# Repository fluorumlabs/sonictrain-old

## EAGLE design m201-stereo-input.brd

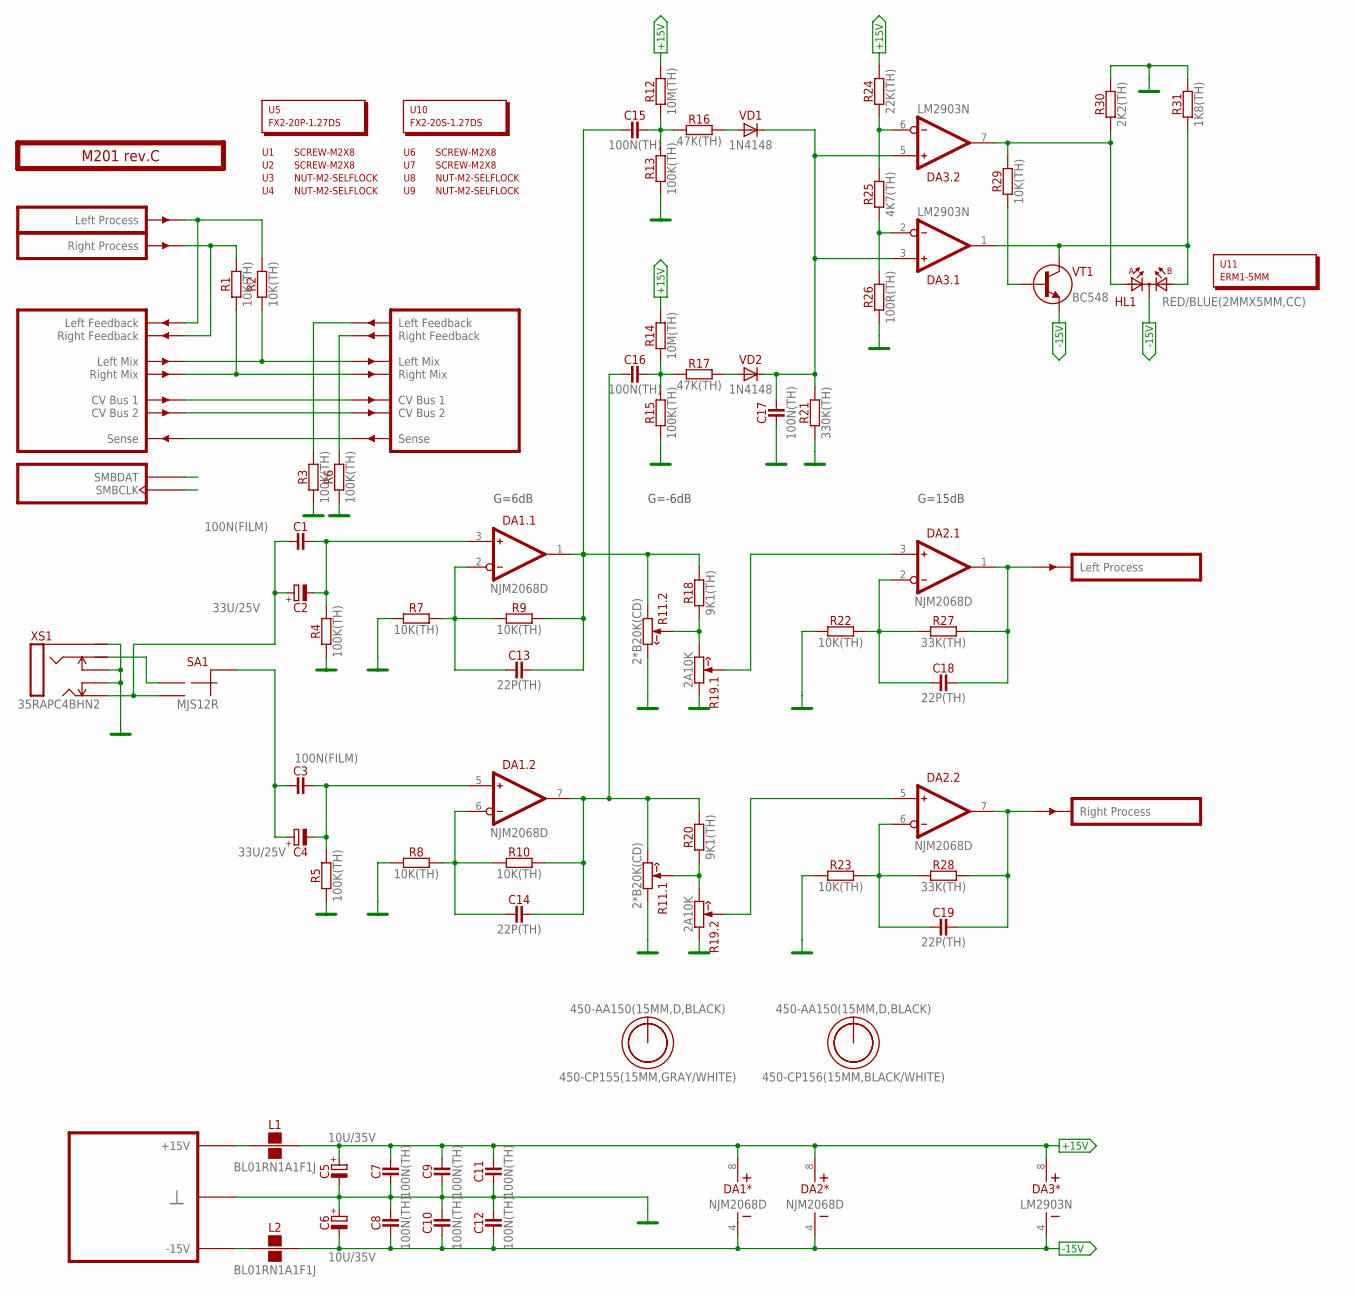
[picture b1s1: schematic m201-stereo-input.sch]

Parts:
C1, C3: 100N(FILM); C050-025X075
C2, C4: 33U/25V; E2,5-7
C5, C6: 10U/35V; E2-5
C7, C8, C9, C10, C11, C12, C15, C16, C17: 100N(TH); C050-024X044
C13, C14, C18, C19: 22P(TH); C050-024X044
DA1, DA2: NJM2068D; DIP-8
DA3: LM2903N; DIP-8
HL1: RED/BLUE(2MMX5MM,CC); LED2X5-3PIN
L1, L2: BL01RN1A1F1J; BL01RN1A
O1, O3: 450-AA150(15MM,D,BLACK); EMPTY
O2: 450-CP155(15MM,GRAY/WHITE); EMPTY
O4: 450-CP156(15MM,BLACK/WHITE); EMPTY
PCB1: M201 rev.C; ST2-BOARD-50
R1, R2, R7, R8, R9, R10, R22, R23, R29: 10K(TH); R-0207/10
R3, R4, R5, R6, R13, R15: 100K(TH); R-0207/10
R11: 2*B20K(CD); RV11-DUAL
R12, R14: 10M(TH); R-0207/10
R16, R17: 47K(TH); R-0207/10
R18, R20: 9K1(TH); R-0207/10
R19: 2A10K; RV11-DUAL
R21: 330K(TH); R-0207/10
R24: 22K(TH); R-0207/10
R25: 4K7(TH); R-0207/10
R26: 100R(TH); R-0207/10
R27, R28: 33K(TH); R-0207/10
R30: 2K2(TH); R-0207/10
R31: 1K8(TH); R-0207/10
SA1: MJS12R; APEM-MJS12R
U1, U2, U6, U7: SCREW-M2X8; EMPTY
U3, U4, U8, U9: NUT-M2-SELFLOCK; EMPTY
U5: FX2-20P-1.27DS; EMPTY
U10: FX2-20S-1.27DS; EMPTY
U11: ERM1-5MM; EMPTY
VD1, VD2: 1N4148; DO35-7
VT1: BC548; TO92
XS1: 35RAPC4BHN2; 35RAP

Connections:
+15V: C5.+, C7.2, C9.2, C11.2, DA1.8 (V+), DA2.8 (V+), DA3.8 (V+), L1.2, R12.2, R14.2, R24.2
-15V: C6.-, C8.1, C10.1, C12.1, DA1.4 (V-), DA2.4 (V-), DA3.4 (V-), HL1.K, L2.2, VT1.3 (E)
GND: C5.-, C6.+, C7.1, C8.2, C9.1, C10.2, C11.1, C12.2, C17.1, PCB1.B4 (GND), PCB1.B4' (GND), PCB1.B5 (GND), PCB1.B5' (GND), PCB1.B6 (GND), PCB1.B6' (GND), PCB1.B7 (GND), PCB1.B7' (GND), PCB1.B8 (GND), PCB1.B8' (GND), R3.1, R4.1, R5.1, R6.1, R7.1, R8.1, R11.1 (CCW), R11.3' (CW), R13.1, R15.1, R19.1 (CCW), R19.1' (CCW), R21.1, R22.1, R23.1, R26.1, R30.2, R31.2, XS1.1 (S), XS1.10 (TN), XS1.11 (RN)
LMIX: PCB1.ALMIX (LMIX), PCB1.ALMIX' (LMIX'), R2.1
unnamed: L1.1, PCB1.A+15 (P+15V), PCB1.A+15' (P+15V), PCB1.B+15 (P+15V), PCB1.B+15' (P+15V)
unnamed: PCB1.ARFBK' (RFBK'), R6.2
unnamed: DA2.3 (IN+), R19.2 (W)
unnamed: PCB1.ALFBK' (LFBK'), R3.2
unnamed: L2.1, PCB1.A-15 (P-15V), PCB1.A-15' (P-15V), PCB1.B-15 (P-15V), PCB1.B-15' (P-15V)
unnamed: SA1.NC (1), XS1.3 (R)
unnamed: C1.1, C2.+, SA1.NO (2), XS1.2 (T)
unnamed: DA2.5 (IN+), R19.2' (W)
unnamed: C3.2, C4.-, DA1.5 (IN+), R5.2
unnamed: C1.2, C2.-, DA1.3 (IN+), R4.2
unnamed: C19.2, DA2.7 (OUT), PCB1.BOUTR' (OUTR), R28.2
unnamed: C18.2, DA2.1 (OUT), PCB1.BOUTL' (OUTL), R27.2
unnamed: C18.1, DA2.2 (IN-), R22.2, R27.1
unnamed: C19.1, DA2.6 (IN-), R23.2, R28.1
unnamed: C14.2, C16.1, DA1.7 (OUT), R10.2, R11.3 (CW), R20.2
unnamed: PCB1.BSENSE (SENSE), PCB1.BSENSE' (SENSE')
unnamed: C15.2, R12.1, R13.2, R16.1
unnamed: C13.2, C15.1, DA1.1 (OUT), R9.2, R11.1' (CCW), R18.2
unnamed: C13.1, DA1.2 (IN-), R7.2, R9.1
unnamed: C14.1, DA1.6 (IN-), R8.2, R10.1
unnamed: R16.2, VD1.A
unnamed: R11.2' (W), R18.1, R19.3 (CW)
unnamed: C16.2, R14.1, R15.2, R17.1
unnamed: R11.2 (W), R19.3' (CW), R20.1
unnamed: C3.1, C4.+, SA1.C (CM)
unnamed: PCB1.ASMBDAT (SMBDAT), PCB1.ASMBDAT' (SMBDAT)
unnamed: PCB1.ARFBK (RFBK), PCB1.BINR (INR), R1.2
unnamed: PCB1.ALFBK (LFBK), PCB1.BINL (INL), R2.2
unnamed: PCB1.ACV1 (CV1), PCB1.ACV1' (CV1')
unnamed: PCB1.ACV2 (CV2), PCB1.ACV2' (CV2')
unnamed: PCB1.ASMBCLK (SMBCLK), PCB1.ASMBCLK' (SMBCLK)
unnamed: R17.2, VD2.A
unnamed: C17.2, DA3.3 (IN+), DA3.5 (IN+), R21.2, VD1.C, VD2.C
unnamed: DA3.2 (IN-), R25.1, R26.2
unnamed: DA3.6 (IN-), R24.1, R25.2
unnamed: DA3.7 (OUT), HL1.A1, R29.2, R30.1
unnamed: R29.1, VT1.2 (B)
unnamed: DA3.1 (OUT), HL1.A2, R31.1, VT1.1 (C)
RMIX: PCB1.ARMIX (RMIX), PCB1.ARMIX' (RMIX'), R1.1

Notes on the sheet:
G=6dB
G=-6dB
G=15dB

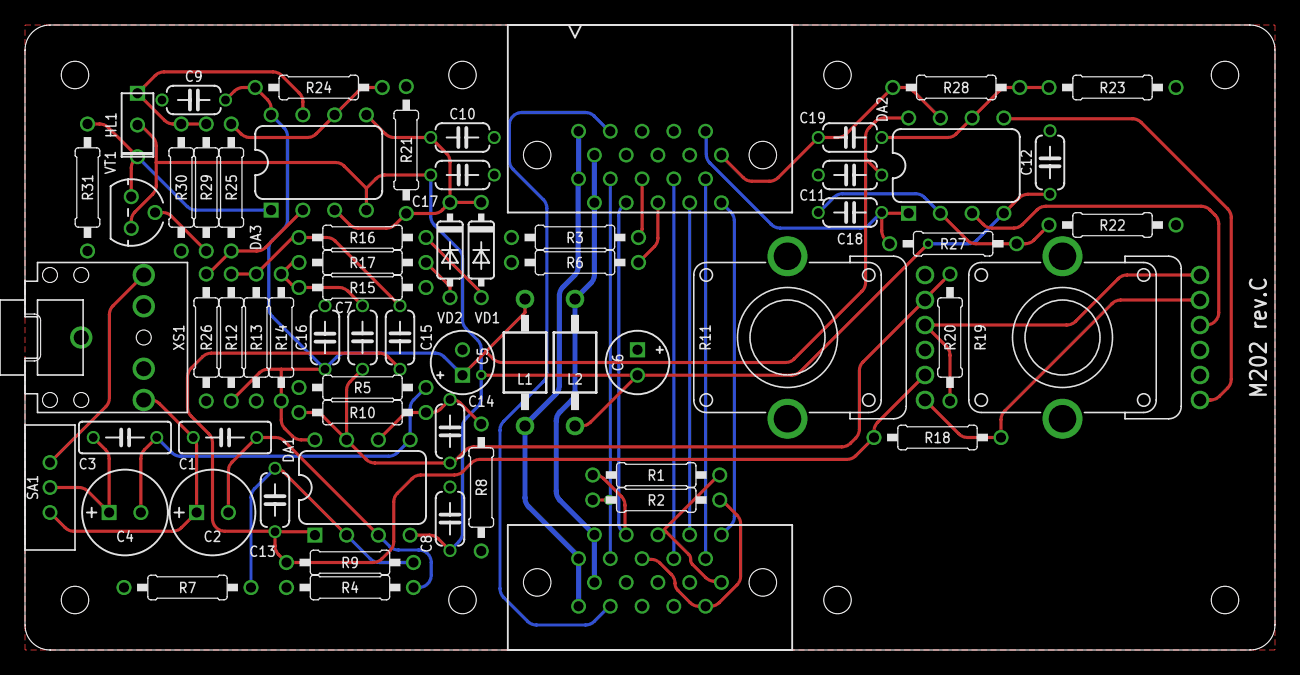
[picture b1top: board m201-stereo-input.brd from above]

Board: 2 copper layers, 100.0 x 50.0 mm, 77 parts (0 on the bottom side), 43 nets.

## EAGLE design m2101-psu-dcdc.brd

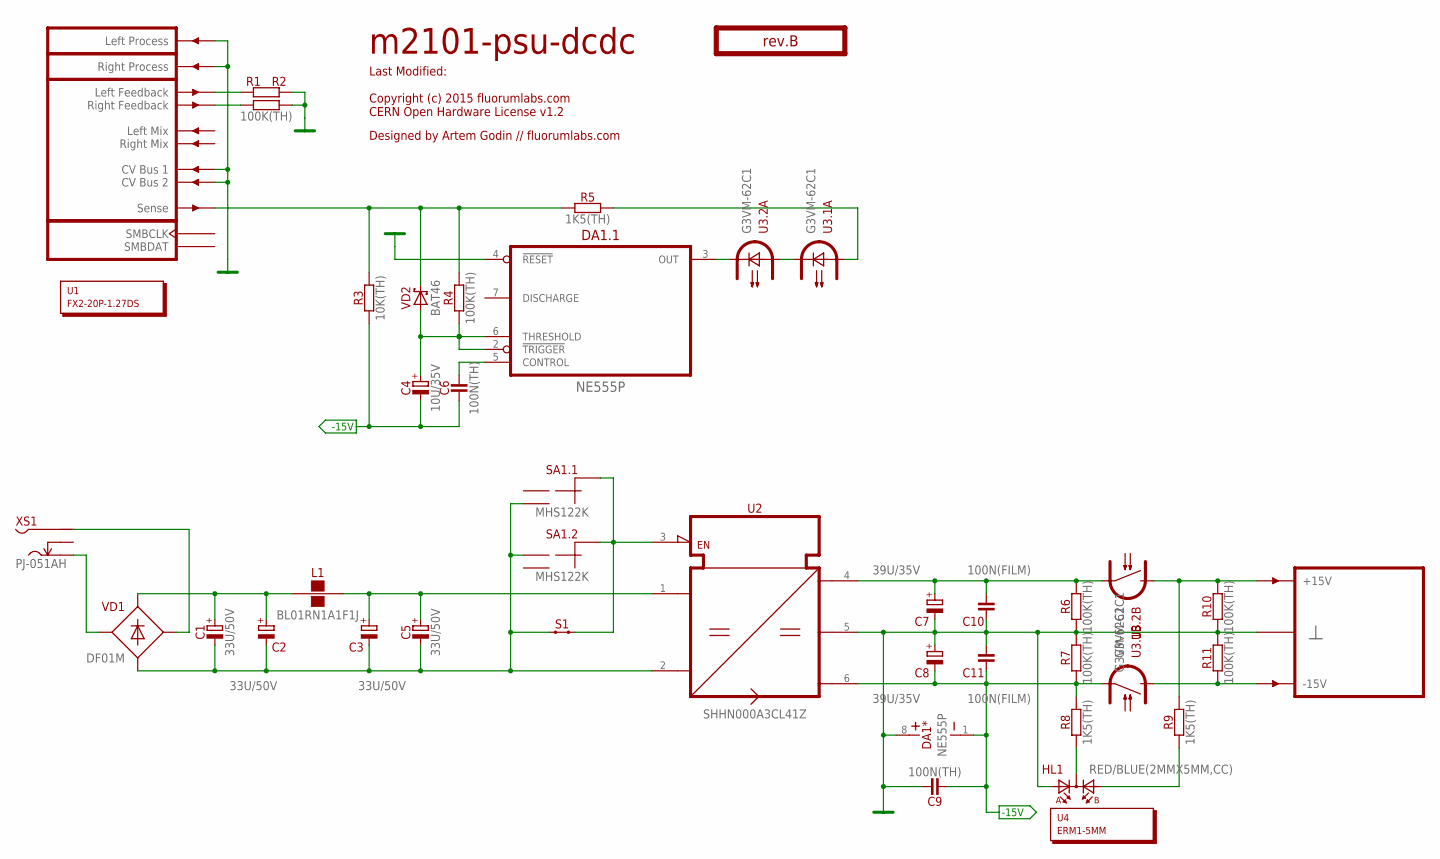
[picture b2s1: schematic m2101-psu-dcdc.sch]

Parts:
C1, C2, C3, C5: 33U/50V; E3,5-8
C4: 10U/35V; E2-5
C6, C9: 100N(TH); C050-024X044
C7, C8: 39U/35V; E3,5-8
C10, C11: 100N(FILM); C050-025X075
DA1: NE555P; DIP-8
HL1: RED/BLUE(2MMX5MM,CC); LED2X5-3PIN
L1: BL01RN1A1F1J; BL01RN1A
O1: Designed by Artem Godin // fluorumlabs.com; EMPTY
PCB1: rev.B; ST2-BOARD-50-PSU
R1, R2, R4, R6, R7, R10, R11: 100K(TH); R-0207/10
R3: 10K(TH); R-0207/10
R5, R8, R9: 1K5(TH); R-0207/10
S1: JUMPER-1POS-SOLDER; JP1-SOLDER
SA1: MHS122K; APEM-MHS122K
U1: FX2-20P-1.27DS; EMPTY
U2: SHHN000A3CL41Z; DC/DC-C1
U3: G3VM-62C1; DIL08
U4: ERM1-5MM; EMPTY
VD1: DF01M; MDIP-4
VD2: BAT46; DO35-7
XS1: PJ-051AH

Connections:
-15V: C4.-, C6.1, C8.-, C9.1, C11.1, DA1.1 (V-), R3.1, R7.1, R8.2, U2.6 (V-), U3.7 (S2)
GND: C7.-, C8.+, C9.2, C10.1, C11.2, DA1.4 (!RESET), DA1.8 (V+), HL1.A1, PCB1.ACV1' (CV1'), PCB1.ACV2' (CV2'), PCB1.B4' (GND), PCB1.B5' (GND), PCB1.B6' (GND), PCB1.B7' (GND), PCB1.B8' (GND), PCB1.BOUTL' (OUTL), PCB1.BOUTR' (OUTR), R1.2, R2.2, R6.1, R7.2, R10.1, R11.2, U2.5 (GND)
unnamed: R5.2, U3.1 (A)
unnamed: VD1.1 (AC1), XS1.3 (S)
unnamed: C1.-, C2.-, C3.-, C5.-, S1.1, SA1.1' (1), SA1.2, U2.2 (IN-), VD1.4 (A)
unnamed: PCB1.ALFBK' (LFBK'), R1.1
unnamed: PCB1.ARFBK' (RFBK'), R2.1
unnamed: C6.2, DA1.5 (CONTROL)
unnamed: DA1.3 (OUT), U3.4 (C)
unnamed: PCB1.A+15' (P+15V), PCB1.B+15' (P+15V), R9.2, R10.2, U3.6 (S1)
unnamed: U3.2 (C), U3.3 (A)
unnamed: C4.+, DA1.2 (!TRIGGER), DA1.6 (THRESHOLD), R4.1, VD2.A
unnamed: VD1.2 (AC2), XS1.1
unnamed: PCB1.A-15' (P-15V), PCB1.B-15' (P-15V), R11.1, U3.8 (S1)
unnamed: HL1.K, R8.1
unnamed: HL1.A2, R9.1
unnamed: C7.+, C10.2, R6.2, U2.4 (V+), U3.5 (S2)
unnamed: S1.2, SA1.CMN (CM), SA1.CMN' (CM), U2.3 (EN)
unnamed: C1.+, C2.+, L1.1, VD1.3 (C)
unnamed: C3.+, C5.+, L1.2, U2.1 (IN+)
SENSE: PCB1.BSENSE' (SENSE'), R3.2, R4.2, R5.1, VD2.C

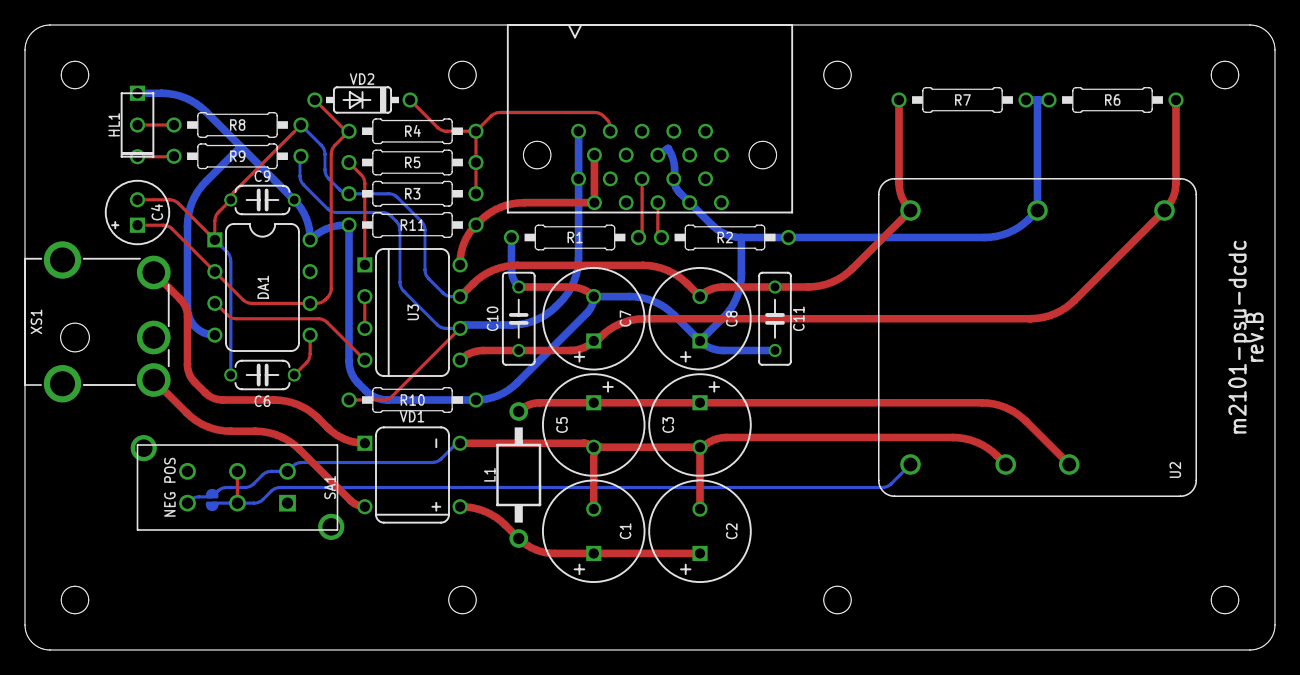
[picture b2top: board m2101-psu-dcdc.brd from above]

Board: 2 copper layers, 100.0 x 50.0 mm, 36 parts (1 on the bottom side), 21 nets.

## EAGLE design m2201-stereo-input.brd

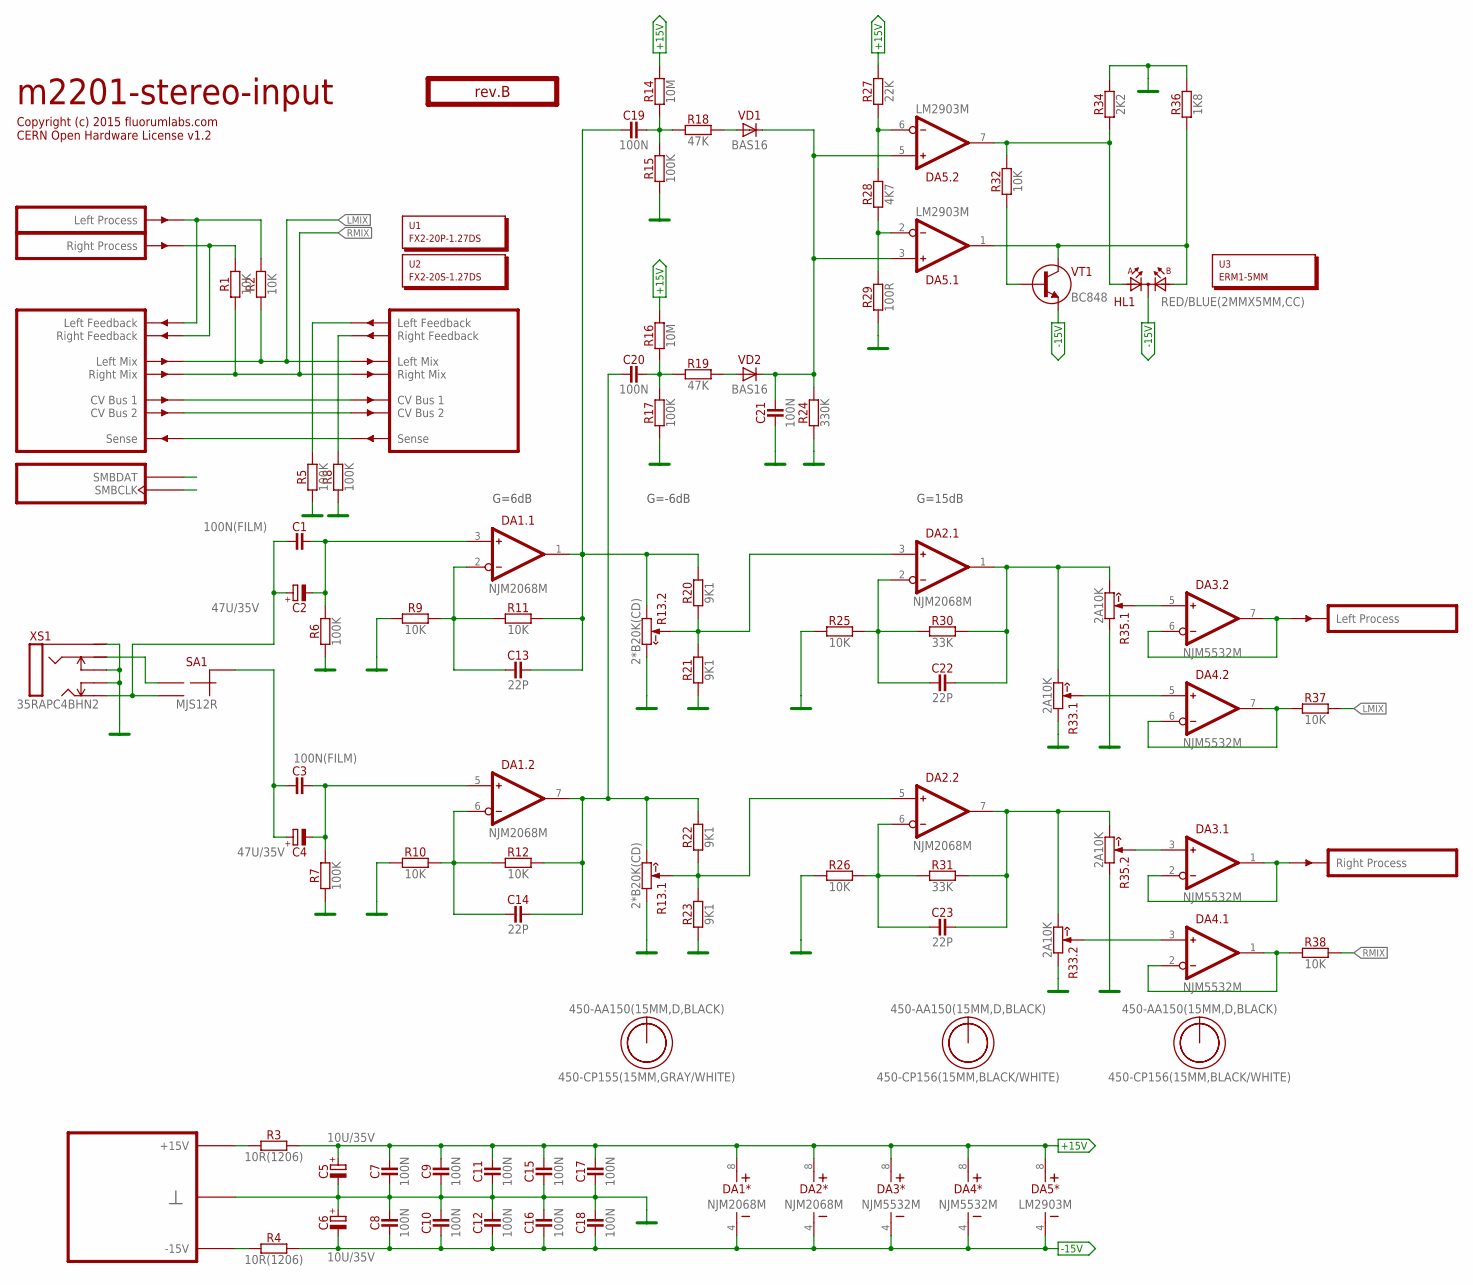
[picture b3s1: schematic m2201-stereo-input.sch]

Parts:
C1, C3: 100N(FILM); C050-025X075
C2, C4: 47U/35V; E3,5-8
C5, C6: 10U/35V; E2-5
C7, C8, C9, C10, C11, C12, C15, C16, C17, C18, C19, C20, C21: 100N; C-0805
C13, C14, C22, C23: 22P; C-0805
DA1, DA2: NJM2068M; SO-8
DA3, DA4: NJM5532M; SO-8
DA5: LM2903M; SO-8
HL1: RED/BLUE(2MMX5MM,CC); LED2X5-3PIN
O1: TITLE; EMPTY
O2, O4, O6: 450-AA150(15MM,D,BLACK); EMPTY
O3: 450-CP155(15MM,GRAY/WHITE); EMPTY
O5, O7: 450-CP156(15MM,BLACK/WHITE); EMPTY
PCB1: rev.B; ST2-BOARD-50
R1, R2, R9, R10, R11, R12, R25, R26, R32, R37, R38: 10K; R-0805
R3, R4: 10R(1206); R-1206
R5, R6, R7, R8, R15, R17: 100K; R-0805
R13: 2*B20K(CD); RV11-DUAL
R14, R16: 10M; R-0805
R18, R19: 47K; R-0805
R20, R21, R22, R23: 9K1; R-0805
R24: 330K; R-0805
R27: 22K; R-0805
R28: 4K7; R-0805
R29: 100R; R-0805
R30, R31: 33K; R-0805
R33, R35: 2A10K; RV11-DUAL
R34: 2K2; R-0805
R36: 1K8; R-0805
SA1: MJS12R; APEM-MJS12R
U1: FX2-20P-1.27DS; EMPTY
U2: FX2-20S-1.27DS; EMPTY
U3: ERM1-5MM; EMPTY
VD1, VD2: BAS16; SOT23
VT1: BC848; SOT23
XS1: 35RAPC4BHN2; 35RAP

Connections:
+15V: C5.+, C7.2, C9.2, C11.2, C15.2, C17.2, DA1.8 (V+), DA2.8 (V+), DA3.8 (V+), DA4.8 (V+), DA5.8 (V+), R3.2, R14.2, R16.2, R27.2
-15V: C6.-, C8.1, C10.1, C12.1, C16.1, C18.1, DA1.4 (V-), DA2.4 (V-), DA3.4 (V-), DA4.4 (V-), DA5.4 (V-), HL1.K, R4.2, VT1.2 (E)
GND: C5.-, C6.+, C7.1, C8.2, C9.1, C10.2, C11.1, C12.2, C15.1, C16.2, C17.1, C18.2, C21.1, PCB1.B4 (GND), PCB1.B4' (GND), PCB1.B5 (GND), PCB1.B5' (GND), PCB1.B6 (GND), PCB1.B6' (GND), PCB1.B7 (GND), PCB1.B7' (GND), PCB1.B8 (GND), PCB1.B8' (GND), R5.1, R6.1, R7.1, R8.1, R9.1, R10.1, R13.1 (CCW), R13.3' (CW), R15.1, R17.1, R21.1, R23.1, R24.1, R25.1, R26.1, R29.1, R33.1 (CCW), R33.1' (CCW), R34.2, R35.1 (CCW), R35.1' (CCW), R36.2, XS1.1 (S), XS1.10 (TN), XS1.11 (RN)
LMIX: PCB1.ALMIX (LMIX), PCB1.ALMIX' (LMIX'), R2.1, R37.2
unnamed: PCB1.A+15 (P+15V), PCB1.A+15' (P+15V), PCB1.B+15 (P+15V), PCB1.B+15' (P+15V), R3.1
unnamed: PCB1.ARFBK' (RFBK'), R8.2
unnamed: DA2.3 (IN+), R13.2' (W), R20.1, R21.2
unnamed: PCB1.ALFBK' (LFBK'), R5.2
unnamed: PCB1.A-15 (P-15V), PCB1.A-15' (P-15V), PCB1.B-15 (P-15V), PCB1.B-15' (P-15V), R4.1
unnamed: SA1.NC (1), XS1.3 (R)
unnamed: C1.1, C2.+, SA1.NO (2), XS1.2 (T)
unnamed: DA2.5 (IN+), R13.2 (W), R22.1, R23.2
unnamed: C3.2, C4.-, DA1.5 (IN+), R7.2
unnamed: C1.2, C2.-, DA1.3 (IN+), R6.2
unnamed: C23.2, DA2.7 (OUT), R31.2, R33.3' (CW), R35.3' (CW)
unnamed: C22.2, DA2.1 (OUT), R30.2, R33.3 (CW), R35.3 (CW)
unnamed: C22.1, DA2.2 (IN-), R25.2, R30.1
unnamed: C23.1, DA2.6 (IN-), R26.2, R31.1
unnamed: C14.2, C20.1, DA1.7 (OUT), R12.2, R13.3 (CW), R22.2
unnamed: PCB1.BSENSE (SENSE), PCB1.BSENSE' (SENSE')
unnamed: C19.2, R14.1, R15.2, R18.1
unnamed: DA3.6 (IN-), DA3.7 (OUT), PCB1.BOUTL' (OUTL)
unnamed: C13.2, C19.1, DA1.1 (OUT), R11.2, R13.1' (CCW), R20.2
unnamed: DA4.6 (IN-), DA4.7 (OUT), R37.1
unnamed: DA3.1 (OUT), DA3.2 (IN-), PCB1.BOUTR' (OUTR)
unnamed: DA4.1 (OUT), DA4.2 (IN-), R38.1
unnamed: DA3.5 (IN+), R35.2 (W)
unnamed: DA4.5 (IN+), R33.2 (W)
unnamed: DA3.3 (IN+), R35.2' (W)
unnamed: C13.1, DA1.2 (IN-), R9.2, R11.1
unnamed: C14.1, DA1.6 (IN-), R10.2, R12.1
unnamed: DA4.3 (IN+), R33.2' (W)
unnamed: R18.2, VD1.1 (A)
unnamed: C20.2, R16.1, R17.2, R19.1
unnamed: C3.1, C4.+, SA1.C (CM)
unnamed: PCB1.ASMBDAT (SMBDAT), PCB1.ASMBDAT' (SMBDAT)
unnamed: PCB1.ARFBK (RFBK), PCB1.BINR (INR), R1.2
unnamed: PCB1.ALFBK (LFBK), PCB1.BINL (INL), R2.2
unnamed: PCB1.ACV1 (CV1), PCB1.ACV1' (CV1')
unnamed: PCB1.ACV2 (CV2), PCB1.ACV2' (CV2')
unnamed: PCB1.ASMBCLK (SMBCLK), PCB1.ASMBCLK' (SMBCLK)
unnamed: R19.2, VD2.1 (A)
unnamed: C21.2, DA5.3 (IN+), DA5.5 (IN+), R24.2, VD1.2 (C), VD2.2 (C)
unnamed: DA5.2 (IN-), R28.1, R29.2
unnamed: DA5.6 (IN-), R27.1, R28.2
unnamed: DA5.7 (OUT), HL1.A1, R32.2, R34.1
unnamed: R32.1, VT1.1 (B)
unnamed: DA5.1 (OUT), HL1.A2, R36.1, VT1.3 (C)
RMIX: PCB1.ARMIX (RMIX), PCB1.ARMIX' (RMIX'), R1.1, R38.2

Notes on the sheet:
G=6dB
G=-6dB
G=15dB

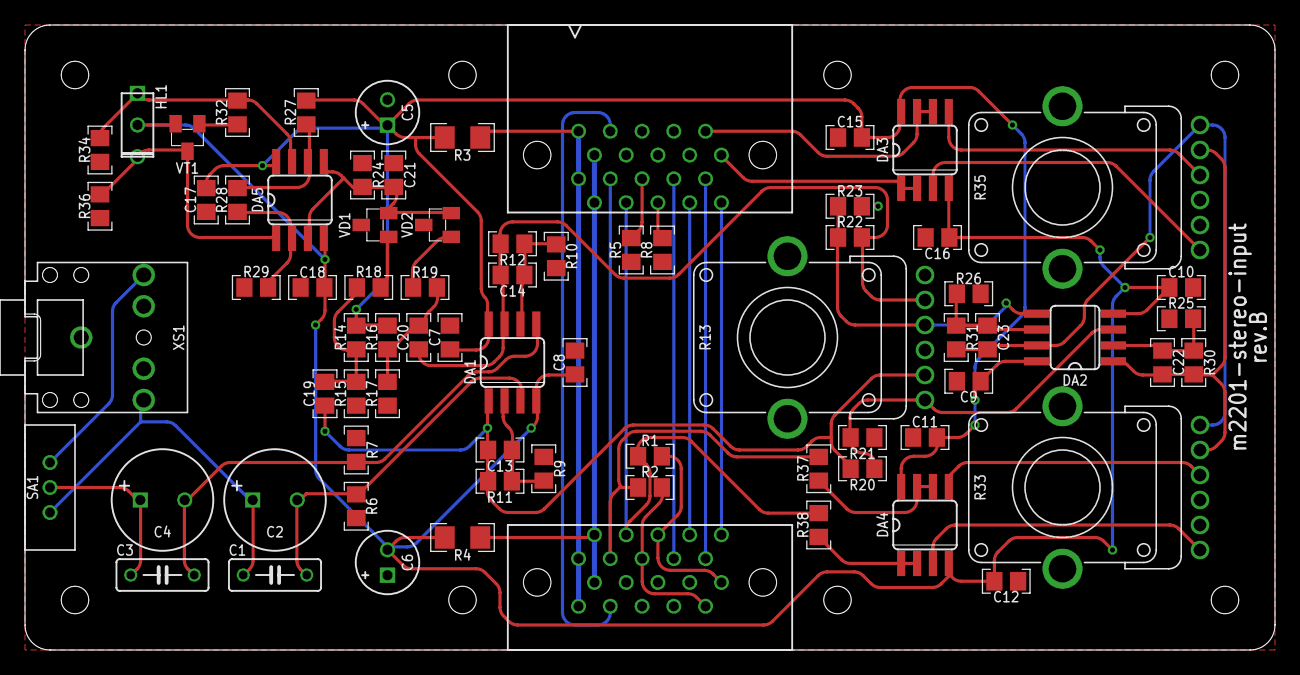
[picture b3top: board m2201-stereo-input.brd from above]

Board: 2 copper layers, 100.0 x 50.0 mm, 83 parts (0 on the bottom side), 49 nets.

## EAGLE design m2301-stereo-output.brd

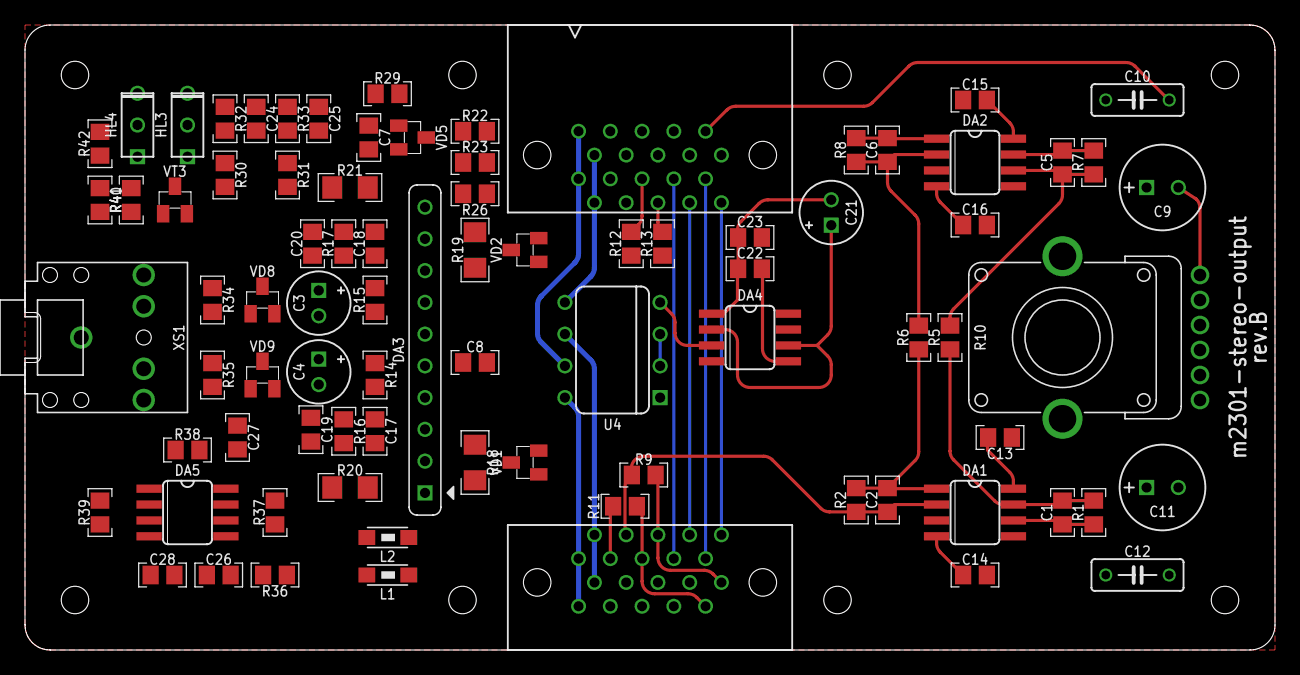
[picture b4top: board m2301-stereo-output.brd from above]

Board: 2 copper layers, 100.0 x 50.0 mm, 89 parts (0 on the bottom side), 52 nets.

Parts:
C1, C2, C5, C6, C17, C18: 22P; C-0805
C3, C4, C21: 10U/35V; E2-5
C7, C8, C13, C14, C15, C16, C19, C20, C22, C23, C24, C25, C26, C27, C28: 100N; C-0805
C9, C11: 33U/25V; E2,5-7
C10, C12: 100N(FILM); C050-025X075
DA1, DA2: NJM2068M; SO-8
DA3: LA6515; SIL10
DA4: NE555D; SO-8
DA5: LM2903M; SO-8
HL3, HL4: RED/BLUE(2MMX5MM,CC); LED2X5-3PIN
L1, L2: BLM31AJ601SN1L; 1206
O1: EMPTY
O2: 450-AA150(15MM,D,BLACK); EMPTY
O3: 450-CP156(15MM,BLACK/WHITE); EMPTY
PCB1: rev.B; ST2-BOARD-50
R1, R2, R5, R6, R7, R8, R9, R11, R14, R15, R22, R41: 10K; R-0805
R10: 2*A10K; RV11-DUAL
R12, R13, R23, R32, R33: 100K; R-0805
R16, R17: 33K; R-0805
R18, R19: 10R(1206); R-1206
R20, R21: 2R(1206); R-1206
R26: 1K5; R-0805
R29: 3K3; R-0805
R30, R31: 10M; R-0805
R34, R35: 47K; R-0805
R36: 330K; R-0805
R37: 22K; R-0805
R38: 4K7; R-0805
R39: 100R; R-0805
R40: 2K2; R-0805
R42: 1K8; R-0805
U1, U7: ERM1-5MM; EMPTY
U4: G3VM-62C1; DIL08
U5: FX2-20P-1.27DS; EMPTY
U6: FX2-20S-1.27DS; EMPTY
VD1, VD2: BAV199; SOT23
VD5, VD8, VD9: BAS16; SOT23
VT3: BC848; SOT23
XS1: 35RAPC4BHN2; 35RAP

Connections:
+15V: C3.+, C7.2, C13.2, C15.2, C27.2, DA1.8, DA2.8, DA3.10, DA5.8, L1.2, R30.2, R31.2, R37.2, VD1.2, VD2.2
-15V: C4.-, C8.1, C14.1, C16.1, C21.-, C22.1, C23.1, C28.1, DA1.4, DA2.4, DA3.5, DA4.1, DA5.4, HL3.K, HL4.K, L2.2, R22.1, VD1.1, VD2.1, VT3.2
CHAIN+15: PCB1.A+15', PCB1.B+15', R29.2, U4.7
GND: C3.-, C4.+, C7.1, C8.2, C13.1, C14.2, C15.1, C16.2, C19.1, C20.1, C23.2, C26.1, C27.1, C28.2, DA1.3, DA1.5, DA2.3, DA2.5, DA4.4, DA4.8, PCB1.B4, PCB1.B4', PCB1.B5, PCB1.B5', PCB1.B6, PCB1.B6', PCB1.B7, PCB1.B7', PCB1.B8, PCB1.B8', PCB1.BSENSE, R10.1, R10.1', R12.1, R13.1, R14.1, R15.1, R32.1, R33.1, R36.1, R39.1, R40.2, R42.2, XS1.1
LMIX: C1.1, DA1.6, PCB1.ALMIX, R1.1, R11.1
unnamed: L1.1, PCB1.A+15, PCB1.B+15, U4.8
unnamed: PCB1.ARFBK', R13.2
unnamed: DA3.6, R10.2
unnamed: PCB1.ALFBK', R12.2
unnamed: L2.1, PCB1.A-15, PCB1.B-15, U4.6
unnamed: C1.2, DA1.7, R1.2, R5.1
unnamed: C2.2, DA1.1, R2.2, R6.1
unnamed: DA3.4, R10.2'
unnamed: C11.-, C12.2, C25.1, PCB1.BOUTR', R10.3
unnamed: C17.2, DA3.1, R16.2, R18.2, R20.2, VD1.3, XS1.2
unnamed: C17.1, DA3.3, R14.2, R16.1
unnamed: R34.2, VD8.1
unnamed: DA3.2, R18.1
unnamed: C9.-, C10.2, C24.1, PCB1.BOUTL', R10.3'
unnamed: C19.2, R20.1
unnamed: C24.2, R30.1, R32.2, R34.1
unnamed: C25.2, R31.1, R33.2, R35.1
unnamed: R35.2, VD9.1
unnamed: C26.2, DA5.3, DA5.5, R36.2, VD8.2, VD9.2
unnamed: C18.1, DA3.7, R15.2, R17.1
unnamed: DA5.2, R38.1, R39.2
unnamed: C18.2, DA3.9, R17.2, R19.2, R21.2, VD2.3, XS1.3
unnamed: DA5.1, HL4.A2, R42.1, VT3.3
unnamed: C22.2, DA4.5
unnamed: C21.+, DA4.2, DA4.6, R23.1, VD5.1
unnamed: R26.2, U4.1
unnamed: DA4.3, U4.4
unnamed: U4.2, U4.3
unnamed: PCB1.ASMBDAT, PCB1.ASMBDAT'
unnamed: PCB1.ARFBK, PCB1.BINR, R9.2
unnamed: PCB1.ALFBK, PCB1.BINL, R11.2
unnamed: PCB1.ACV1, PCB1.ACV1'
unnamed: PCB1.ACV2, PCB1.ACV2'
unnamed: PCB1.ASMBCLK, PCB1.ASMBCLK'
unnamed: HL3.A2, R29.1
unnamed: DA3.8, R19.1
unnamed: C20.2, R21.1
unnamed: DA5.6, R37.1, R38.2
unnamed: DA5.7, HL4.A1, R40.1, R41.2
unnamed: R41.1, VT3.1
unnamed: PCB1.A-15', PCB1.B-15', U4.5
unnamed: C5.1, DA2.6, R5.2, R7.1
unnamed: C5.2, C9.+, C10.1, DA2.7, R7.2
unnamed: C6.1, DA2.2, R6.2, R8.1
unnamed: C6.2, C11.+, C12.1, DA2.1, R8.2
RMIX: C2.1, DA1.2, PCB1.ARMIX, R2.1, R9.1
SENSE: PCB1.BSENSE', R22.2, R23.2, R26.1, VD5.2

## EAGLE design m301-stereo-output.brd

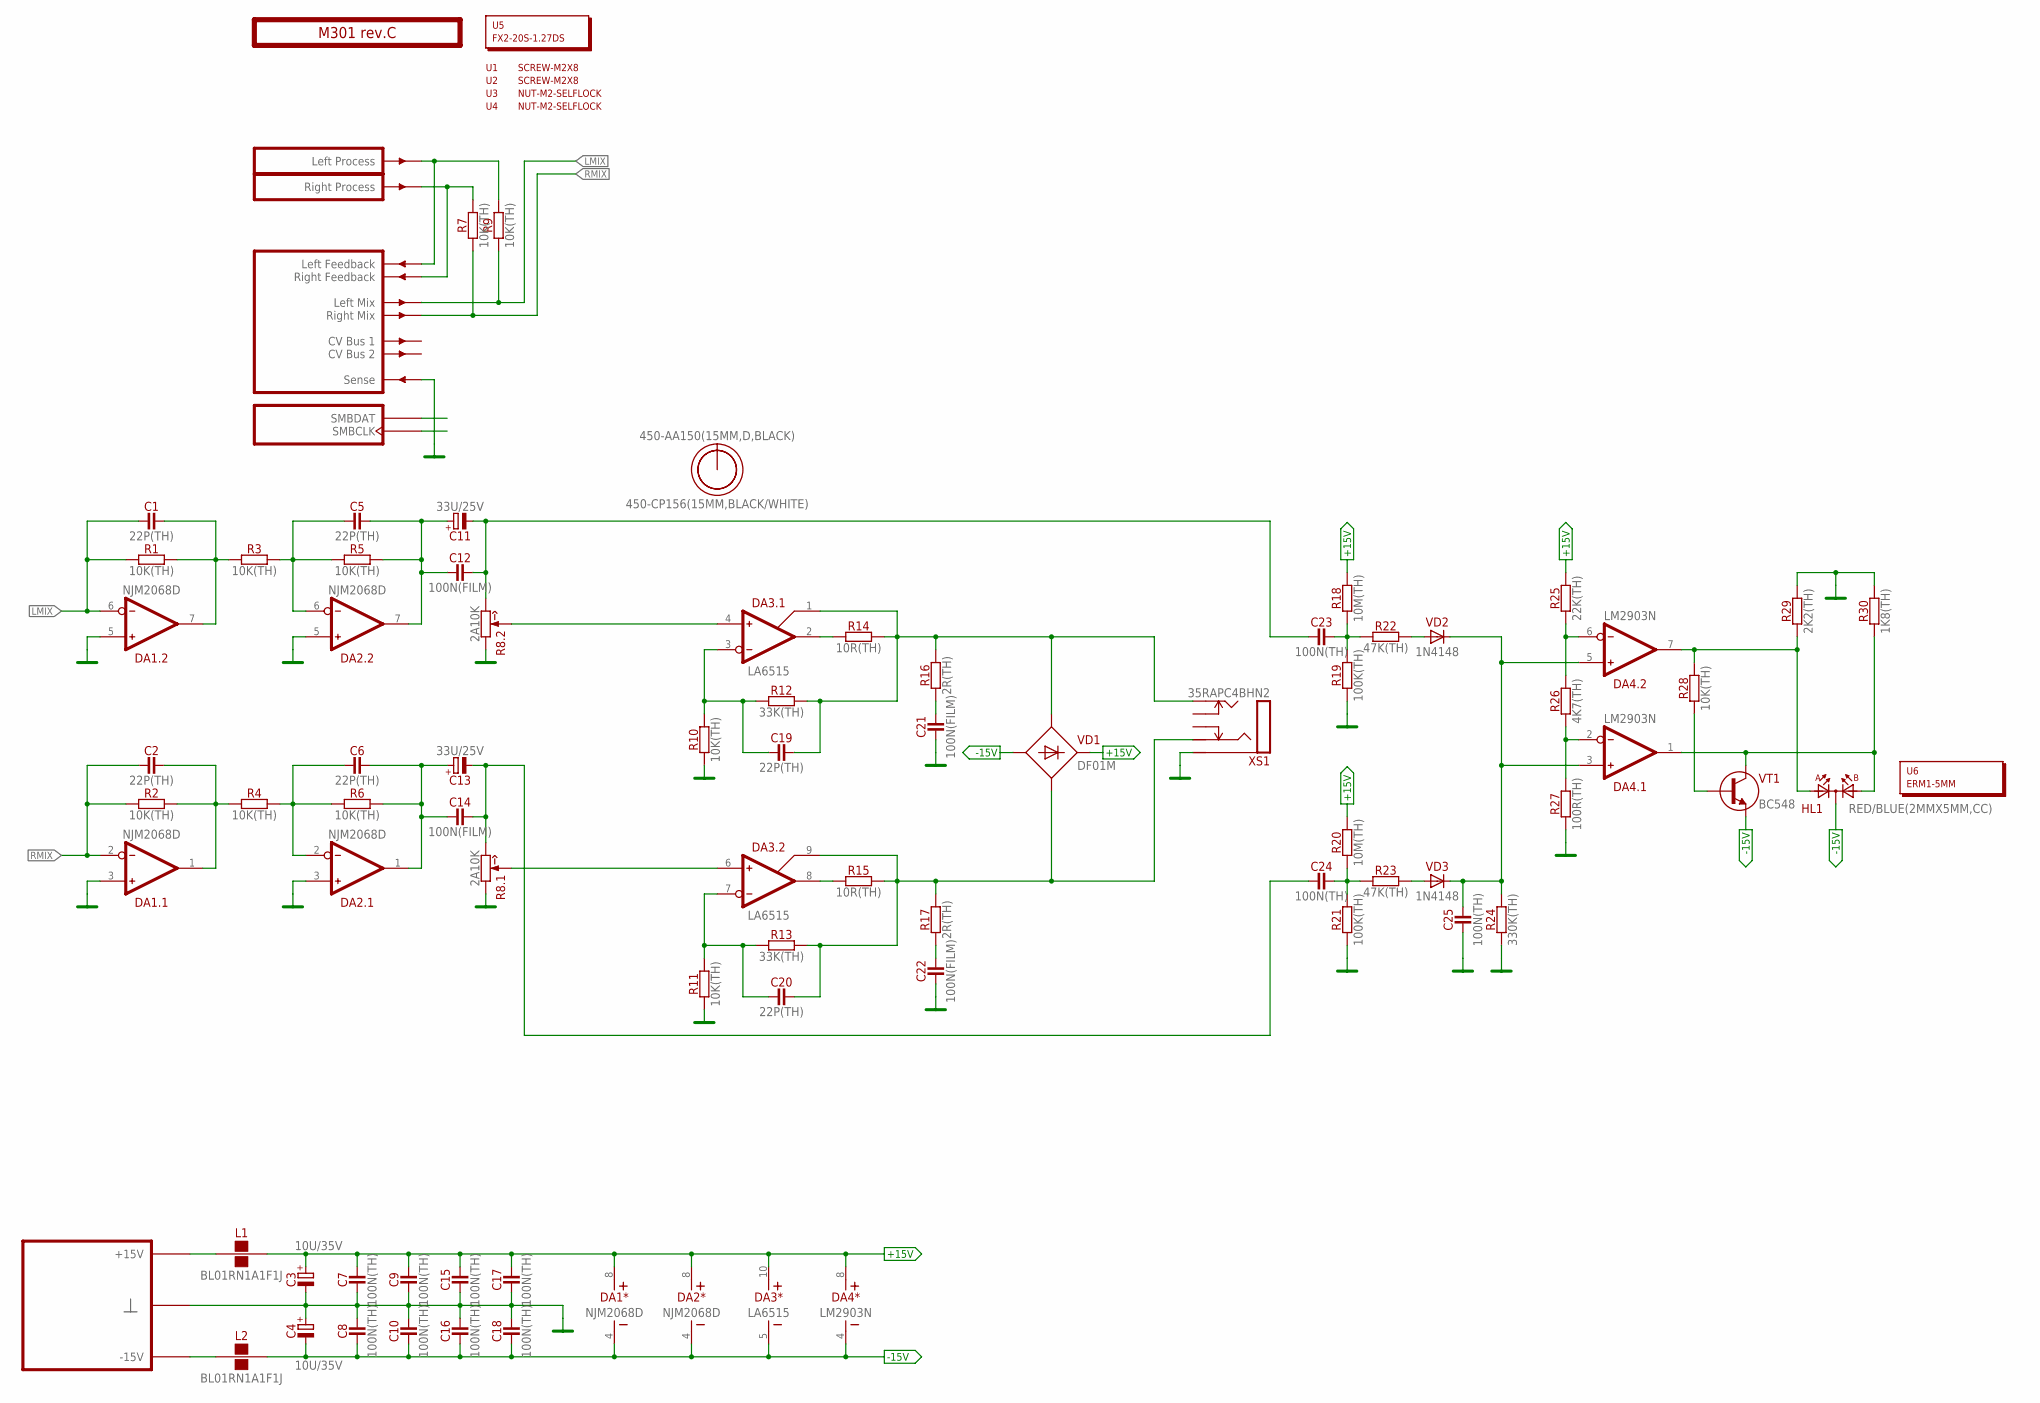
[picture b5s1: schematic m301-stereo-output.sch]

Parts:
C1, C2, C5, C6, C19, C20: 22P(TH); C050-024X044
C3, C4: 10U/35V; E2-5
C7, C8, C9, C10, C15, C16, C17, C18, C23, C24, C25: 100N(TH); C050-024X044
C11, C13: 33U/25V; E2,5-7
C12, C14, C21, C22: 100N(FILM); C050-025X075
DA1, DA2: NJM2068D; DIP-8
DA3: LA6515; SIL10
DA4: LM2903N; DIP-8
HL1: RED/BLUE(2MMX5MM,CC); LED2X5-3PIN
L1, L2: BL01RN1A1F1J; BL01RN1A
O1: 450-AA150(15MM,D,BLACK); EMPTY
O2: 450-CP156(15MM,BLACK/WHITE); EMPTY
PCB1: M301 rev.C; ST2-BOARD-50-END
R1, R2, R3, R4, R5, R6, R7, R9, R10, R11, R28: 10K(TH); R-0207/10
R8: 2A10K; RV11-DUAL
R12, R13: 33K(TH); R-0207/10
R14, R15: 10R(TH); R-0207/10
R16, R17: 2R(TH); R-0207/10
R18, R20: 10M(TH); R-0207/10
R19, R21: 100K(TH); R-0207/10
R22, R23: 47K(TH); R-0207/10
R24: 330K(TH); R-0207/10
R25: 22K(TH); R-0207/10
R26: 4K7(TH); R-0207/10
R27: 100R(TH); R-0207/10
R29: 2K2(TH); R-0207/10
R30: 1K8(TH); R-0207/10
U1, U2: SCREW-M2X8; EMPTY
U3, U4: NUT-M2-SELFLOCK; EMPTY
U5: FX2-20S-1.27DS; EMPTY
U6: ERM1-5MM; EMPTY
VD1: DF01M; MDIP-4
VD2, VD3: 1N4148; DO35-7
VT1: BC548; TO92
XS1: 35RAPC4BHN2; 35RAP

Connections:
+15V: C3.+, C7.2, C9.2, C15.2, C17.2, DA1.8 (V+), DA2.8 (V+), DA3.10 (V+), DA4.8 (V+), L1.2, R18.2, R20.2, R25.2, VD1.3 (C)
-15V: C4.-, C8.1, C10.1, C16.1, C18.1, DA1.4 (V-), DA2.4 (V-), DA3.5 (V-), DA4.4 (V-), HL1.K, L2.2, VD1.4 (A), VT1.3 (E)
GND: C3.-, C4.+, C7.1, C8.2, C9.1, C10.2, C15.1, C16.2, C17.1, C18.2, C21.1, C22.1, C25.1, DA1.3 (IN+), DA1.5 (IN+), DA2.3 (IN+), DA2.5 (IN+), PCB1.B4 (GND), PCB1.B5 (GND), PCB1.B6 (GND), PCB1.B7 (GND), PCB1.B8 (GND), PCB1.BSENSE (SENSE), R8.1 (CCW), R8.1' (CCW), R10.1, R11.1, R19.1, R21.1, R24.1, R27.1, R29.2, R30.2, XS1.1 (S)
LMIX: C1.1, DA1.6 (IN-), PCB1.ALMIX (LMIX), R1.1, R9.1
unnamed: L1.1, PCB1.A+15 (P+15V), PCB1.B+15 (P+15V)
unnamed: DA3.6 (IN+), R8.2 (W)
unnamed: L2.1, PCB1.A-15 (P-15V), PCB1.B-15 (P-15V)
unnamed: C1.2, DA1.7 (OUT), R1.2, R3.1
unnamed: C2.2, DA1.1 (OUT), R2.2, R4.1
unnamed: DA3.4 (IN+), R8.2' (W)
unnamed: C13.-, C14.2, C24.1, R8.3 (CW)
unnamed: C19.2, DA3.1 (SENSE), R12.2, R14.2, R16.2, VD1.1 (AC1), XS1.2 (T)
unnamed: C19.1, DA3.3 (IN-), R10.2, R12.1
unnamed: R22.2, VD2.A
unnamed: DA3.2 (OUT), R14.1
unnamed: C11.-, C12.2, C23.1, R8.3' (CW)
unnamed: C21.2, R16.1
unnamed: C23.2, R18.1, R19.2, R22.1
unnamed: C24.2, R20.1, R21.2, R23.1
unnamed: R23.2, VD3.A
unnamed: C25.2, DA4.3 (IN+), DA4.5 (IN+), R24.2, VD2.C, VD3.C
unnamed: C20.1, DA3.7 (IN-), R11.2, R13.1
unnamed: DA4.2 (IN-), R26.1, R27.2
unnamed: C20.2, DA3.9 (SENSE), R13.2, R15.2, R17.2, VD1.2 (AC2), XS1.3 (R)
unnamed: DA4.1 (OUT), HL1.A2, R30.1, VT1.1 (C)
unnamed: PCB1.ARFBK (RFBK), PCB1.BINR (INR), R7.2
unnamed: PCB1.ALFBK (LFBK), PCB1.BINL (INL), R9.2
unnamed: DA3.8 (OUT), R15.1
unnamed: C22.2, R17.1
unnamed: DA4.6 (IN-), R25.1, R26.2
unnamed: DA4.7 (OUT), HL1.A1, R28.2, R29.1
unnamed: R28.1, VT1.2 (B)
unnamed: C5.1, DA2.6 (IN-), R3.2, R5.1
unnamed: C5.2, C11.+, C12.1, DA2.7 (OUT), R5.2
unnamed: C6.1, DA2.2 (IN-), R4.2, R6.1
unnamed: C6.2, C13.+, C14.1, DA2.1 (OUT), R6.2
RMIX: C2.1, DA1.2 (IN-), PCB1.ARMIX (RMIX), R2.1, R7.1

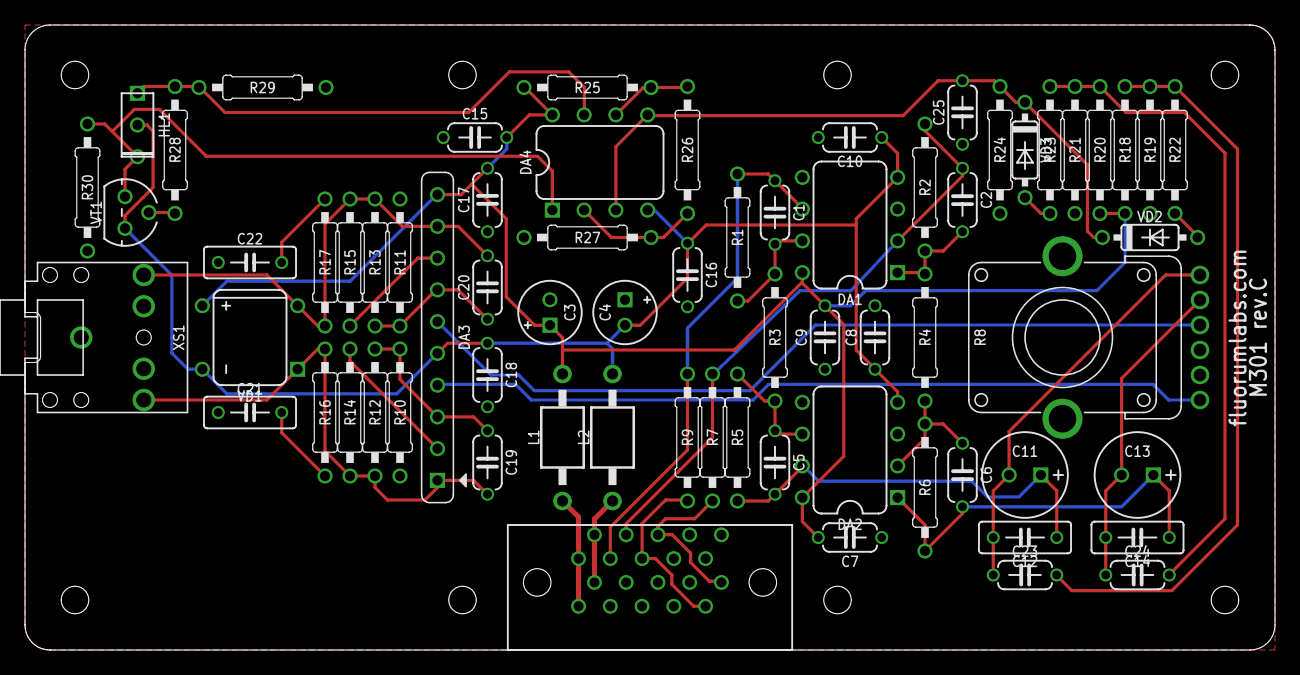
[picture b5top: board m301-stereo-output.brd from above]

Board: 2 copper layers, 100.0 x 50.0 mm, 76 parts (0 on the bottom side), 37 nets.

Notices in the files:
parts and their libraries:
text: Last Modified:
Copyright (c) 2015 fluorumlabs.com
CERN Open Hardware License v1.2
